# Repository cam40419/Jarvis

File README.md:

# Simon

**SIMON: Somehow It Manages Our Nonsense.**

Simon is a local-first foundation for a hosted AI work platform. Its browser workspace
currently provides shared projects, task boards, human membership and scoped agent teams,
alongside independent conversations. PostgreSQL persists project and identity records.

In **Projects**, describe an outcome, create tasks, and assign work to a person, an agent
or the shared pool. **Agents** defines each role's responsibilities, success criteria and
reason for joining the team. Owners control team size, delegated staffing and temporary
worker access. Pausing or retiring an agent returns unfinished assignments to the pool.

**Intake** accepts versioned source files, uses a configured model to propose the next
milestone and team, and makes a separate model review before applying roles and board work.
**Models & usage** provides write-only project keys, deliberate model qualification,
separate planning/review routes, and shared project/workspace spending and call limits.
Projects control hosted/paid consent and automatic staffing. Unknown usage remains held
until settled or reconciled with evidence. **Execution** queues bounded agent workflows,
tracks checkpoints, dependencies, questions, delegation and schedules, and saves text
candidates for review. An optional outbound runner advances server-side steps under a
separate owner grant. **Artifacts & review** saves immutable output versions, performs
independent text review, records exact-version acceptance and creates linked repair work
from owner feedback. **Delivery packets** bundles exact originals, safe source previews,
checks, decisions and limitations, with immutable history and current-access checks.
Compute/storage entitlements and broader quality evaluation remain
subsequent core work. Creating a role does not start a worker.
The old Work interface, manifest dispatcher and separate project/task authorities have
been removed. There is no legacy-project migration or compatibility mode.

## Run locally

Use Python 3.11+ and a local virtual environment:

```powershell
python -m venv venv
.\venv\Scripts\python.exe -m pip install -e '.[dev,postgres]'
```

Configure `.env` from [.env.example](.env.example). For a configured local installation,
start the Compose database with `.\scripts\start-local.ps1 -DatabaseOnly` when using that local database, then start the configured server with `.\scripts\start-local.ps1` and open
**http://localhost:8000/login**. Independent queued conversations use
`.\scripts\start-assistant-worker.ps1`; this does not execute native board tasks.
New installations can use `.\scripts\start-dev.ps1 -Memory -TestRunner` for a
nonpersistent smoke run. Follow [identity setup](docs/runbooks/identity.md) and
[local operations](docs/runbooks/local-operations.md) for persistent accounts.

## Guides

- [Projects, scoped agents and team management](docs/runbooks/native-projects.md)
- [AI-assisted intake and automatic staffing](docs/runbooks/project-intake.md)
- [Project models, encrypted keys and resource limits](docs/runbooks/project-models.md)
- [Native execution, durable workflows and runners](docs/runbooks/native-execution.md)
- [Artifacts, independent review and owner revisions](docs/runbooks/native-artifacts.md)
- [Roadmap and delivery order](docs/next-phases.md)
- [Platform architecture and implementation backlog](docs/architecture/autonomous-work-platform-plan.md)
- [Clothing-brand pilot and core acceptance](docs/architecture/clothing-brand-pilot-charter.md)
- [Integration work packages](docs/architecture/integration-delivery-plan.md)
- [Hosting and subscription capacity](docs/architecture/hosting-and-capacity-plan.md)
- [Development standards](docs/development.md)
- [Isolated database testing](docs/runbooks/database-testing.md)
- [Storage recovery](docs/runbooks/storage-recovery.md) and [remote access](docs/runbooks/remote-access.md)

The platform is the deliverable; stdout is its pilot. Complete and test the core before
accepting individual business tools. Existing generic adapters are reusable implementation
components, not accepted native-project integrations.

## Verify

```powershell
.\venv\Scripts\python.exe -m ruff check src tests scripts examples
.\venv\Scripts\python.exe -m ruff format --check src tests scripts examples
.\venv\Scripts\python.exe -m mypy src
.\venv\Scripts\python.exe -m pytest -q -m "not postgres and not browser and not live"
npm run format:check
npm run lint
```

PostgreSQL tests use an isolated database ending in `_test`; the database runbook describes
the disposable-cluster runner. Browser tests use `SIMON_BROWSER_TESTS=1` and installed
Playwright Chromium or `SIMON_BROWSER_CHANNEL=msedge`. Normal acceptance uses synthetic
providers. Paid model tests require separate explicit opt-in.

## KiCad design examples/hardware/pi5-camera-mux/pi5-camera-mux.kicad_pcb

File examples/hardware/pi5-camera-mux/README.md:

# Raspberry Pi 5 four-camera selector: engineering prototype

This review project connects **four IMX219 Camera Module 2 cameras, with one CSI
camera selected at a time**, to a Raspberry Pi 5 camera connector. It implements
three two-to-one TS3DV642-Q1 switches, a PCA9544A I2C selector at address `0x70`,
and a separately supplied camera rail. It is a CAD prototype awaiting physical
electrical, signal-integrity, cable and Raspberry Pi software validation.

**Use an external regulated, current-limited 3.3 V supply at J7.** Never connect
5 V to that header. The Pi connector powers the switch/control rail; it does not
supply the four camera modules. A TPS22918 gates the external camera rail from
the Pi's 3.3 V presence. It is not a regulator, current limiter or reverse-current
protector. A 1.5 A current limit is an initial bench setup, not a measured demand
or guaranteed operating budget. All four modules may be powered for enumeration.

## Review files

- Open `pi5-camera-mux.kicad_pro` in KiCad 9; the corresponding schematic and PCB
  are editable source. `CameraMux.kicad_sym` and library tables accompany them.
- `review/schematic.pdf` and `review/board.png` provide browser previews.
- `review/schematic-details.pdf` retains the master and adds nine enlarged A4
  section pages for reading and printing; its companion JSON records provenance.
- `review/bom.csv`, `review/connectivity.net`, and `review/gerbers-review.zip`
  provide the BOM, actual exported netlist, and Gerber/Excellon review package.
- `review/erc.json`, `review/drc.json`, and `review/tool-smoke.json` contain the
  actual KiCad tool results. A nonzero violation count remains a release hold.
- `connectivity-review.json` and `review/layout-review.json` record independent
  pin, board/netlist, trace-length, layer, via and plane observations.
- [engineering-review.md](engineering-review.md) records manufacturer references,
  component pin tables, power/driver analysis and the outstanding release checks.

The Gerber ZIP is for engineering review. Do not order or assemble this revision
until the documented release holds have been resolved by an electronics reviewer.

Validation recorded on 2026-10-01 UTC with KiCad 9.0.2:

- All seven isolated PCB operations completed successfully. ERC: **0 violations**.
  DRC: **0 violations, 0 missing connections, 0 schematic-parity issues**.
- The workspace Python tool successfully invoked Debian's `pcbnew` interpreter
  to load and save an editable board; source hashes remained unchanged and the
  container lease was released. An attempted output overwrite was rejected.
- Independent review passed **225 netlist checks**, found no board-pad/netlist
  mismatches, and confirmed all 42 CSI nets are simple, unbranched front-layer
  paths. All 21 measured pairs have **0.0000 mm P/N difference** and zero vias.
- All **24,438 ground-reference samples** beneath CSI traces fall within one
  filled In1 ground region. This is sampled geometry, not electromagnetic analysis.
- Selected board copper paths measure **109.5515–113.6643 mm**, excluding switch
  packages and cables. Lane-to-clock length differences and total insertion loss
  remain subjects for signal-integrity qualification and physical tests.

The reviewed board SHA-256 is
`dcc29d94eef476e0034d6c41a2a14266b6fae18dcd7bfd40f2587fa7990fcb64`.
No physical board, camera capture, impedance measurement or fabrication was performed.

## Connections and assembly

| Connector | Purpose | Key details |
| --- | --- | --- |
| J1 | Pi 5 host | Amphenol F32Q-1A7H1-11022, 22 positions, 0.5 mm, top contacts |
| J2/J3/J4/J5 | Cameras A/B/C/D | TE 1-84953-5, 15 positions, 1 mm, top contacts |
| J6 | Pi GPIO control | Pins 1–4: GND, GPIO4, GPIO17, GPIO18 |
| J7 | External camera power | Pin 1 regulated 3.3 V; pin 2 common ground |

Camera connector pin 11 shares the host camera-enable IO0. Pin 12 IO1 connects
through separate **DNP** zero-ohm links R16–R19; leave all four links unfitted for
Camera Module 2, whose official schematic marks pin 12 unconnected. R6/R7 host
I2C pull-ups are also DNP. Check the combined module/board pull-up resistance
before fitting the downstream pull-ups R8–R15.

Read board pin-1 markings and manufacturer contact drawings, and verify every
cable's conductor continuity before applying power. A pitch adapter cable alone
does not establish contact orientation. The TE signal/mounting-pad drawing review
is recorded in the engineering review; actual mating cable clearances, connector
samples and host cable orientation still require assembly validation.
On the board top view, pin 1 is below the last/supply pin on all five FFC
connectors. J1's host cable may extend over the board: confirm insertion direction,
actuator access and physical cable clearance with the actual connector samples.

The GPIO4/18/17 selection states are A=`0/1/0`, B=`1/1/0`, C=`0/0/1`,
D=`1/0/1`. GPIO pull-downs disable both leaf switches at reset. Do not switch
cameras during capture. Use a reviewed device-tree/libcamera configuration to
coordinate video selection and I2C selection; the candidate official overlay in
the engineering review has not been tested on this physical board.

## Layout intent and limits

The board is 125 × 110 mm with four copper layers: F.Cu carries the paired CSI
paths, In1.Cu supplies their ground reference, In2.Cu distributes camera power,
and B.Cu carries control/auxiliary routes. The CSI paths use 0.15 mm copper and
0.22 mm pair gap in their trunks, with short symmetric pad fanouts and no signal
vias. These dimensions are geometric choices, **not a verified 100-ohm stack-up**.

The independent layout report measures each of 21 differential pairs and the
three board segments in each selectable path. Package internals and FFC cables
are excluded. Two switch stages, path length, connector discontinuities and
the actual fabricated stack-up require signal-integrity review and bench tests.
Ground plane fill is checked geometrically; this does not replace return-current
and via-antipad review. Plane necks, supply drop, inrush, thermal behavior and
backfeeding under every power sequence require measurement.

## Reproducing the CAD workflow

Use a **copy** of this directory. Generation replaces the source board with the
deterministic placement and locked paired routes; the final low-speed routing
comes from the separately imported router session. Ground/power vias are fixed
before routing; KiCad supplies the final internal-plane fill after import. The
router receives those fixed conductors without plane polygons, avoiding its
incomplete SMD-to-plane handling on disabled inner routing layers.

```powershell
docker build -f deploy/Dockerfile.pcb-worker -t simon-pcb:local .
docker build -f deploy/Dockerfile.pcb-router -t simon-pcb-router:local .
$pcbProject = (Resolve-Path 'path/to/project-copy').Path
docker run --rm --network none --mount "type=bind,source=$pcbProject,target=/workspace" --entrypoint /usr/bin/python3 simon-pcb:local /workspace/generate.py
docker run --rm --hostname localhost --network none --cpus 2 --memory 2g --mount "type=bind,source=$pcbProject,target=/workspace" --entrypoint /opt/java/openjdk/bin/java simon-pcb-router:local -jar /opt/freerouting.jar -de /workspace/pi5-camera-mux.dsn -do /workspace/pi5-camera-mux.ses --gui.enabled=false -mp 20 -mt 0 --router.layers.routable=true,false,false,true -da --api_server.enabled=false --user_data_path=/tmp/freerouting
docker run --rm --network none --mount "type=bind,source=$pcbProject,target=/workspace" --entrypoint /usr/bin/python3 simon-pcb:local /workspace/finish_routing.py
```

The optional router image pins Freerouting 2.4.1 by SHA-256 and uses Java 25.
Routing runs offline, preserves fixed CSI geometry, and may require manual
completion/review after tool or library changes. Inspect actual DRC rather than
assuming an autorouter's completion message establishes a correct board.

From the repository root, refresh real isolated-tool exports with
`python examples/agents/pcb_smoke.py --write-review`. Refresh the independent
connectivity audit with `python examples/hardware/pi5-camera-mux/review_connectivity.py`.
Run `review_layout.py` using KiCad's `/usr/bin/python3` and save its JSON output.
`render_preview.py` rasterizes the actual SVG using PyMuPDF; `schematic_details.py`
uses the same development dependency to create vector-preserving enlarged pages.
These scripts use no model/provider calls. See the
[PCB tool runbook](../../../docs/runbooks/agent-pcb.md) for authorization and limits.

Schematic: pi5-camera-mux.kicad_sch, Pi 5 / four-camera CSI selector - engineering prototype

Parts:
C1, C2, C3, C4: 100nF; C_0603_1608Metric
C5, C6: 10uF_10V_X5R; C_0805_2012Metric
C7: 1nF; C_0603_1608Metric
J1: F32Q-1A7H1-11022_HOST; Amphenol_F32Q-1A7x1-11022_1x22-1MP_P0.5mm_Horizontal
J2: TE_1-84953-5_CAM_A; TE_1-84953-5_1x15-1MP_P1.0mm_Horizontal
J3: TE_1-84953-5_CAM_B; TE_1-84953-5_1x15-1MP_P1.0mm_Horizontal
J4: TE_1-84953-5_CAM_C; TE_1-84953-5_1x15-1MP_P1.0mm_Horizontal
J5: TE_1-84953-5_CAM_D; TE_1-84953-5_1x15-1MP_P1.0mm_Horizontal
J6: GPIO_GND_4_17_18; PinHeader_1x04_P2.54mm_Vertical
J7: REGULATED_3V3_INPUT; PinHeader_1x02_P2.54mm_Vertical
R1, R2, R3: 10k; R_0603_1608Metric
R4: 100k; R_0603_1608Metric
R5: 100R; R_0603_1608Metric
R6, R7: 4.7k_DNP; R_0603_1608Metric; not fitted
R8, R9, R10, R11, R12, R13, R14, R15: 4.7k; R_0603_1608Metric
R16, R17, R18, R19: 0R_DNP_IO1; R_0603_1608Metric; not fitted
U1, U2, U3: TS3DV642RUARQ1; WQFN-42-1EP_3.5x9mm_P0.5mm_EP2.05x7.55mm
U4: PCA9544APWR_ADDR_0x70; Texas_PW0020A_TSSOP-20_4.4x6.5mm_P0.65mm
U5: TPS22918DBVR; SOT-23-6

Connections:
/BANK_AB_CLK_N: U1.37 (D0-A), U2.6 (D0-)
/BANK_AB_CLK_P: U1.38 (D0+A), U2.5 (D0+)
/BANK_AB_D0_N: U1.33 (D2-A), U2.11 (D2-)
/BANK_AB_D0_P: U1.34 (D2+A), U2.10 (D2+)
/BANK_AB_D1_N: U1.35 (D1-A), U2.8 (D1-)
/BANK_AB_D1_P: U1.36 (D1+A), U2.7 (D1+)
/BANK_CD_CLK_N: U1.28 (D0-B), U3.6 (D0-)
/BANK_CD_CLK_P: U1.29 (D0+B), U3.5 (D0+)
/BANK_CD_D0_N: U1.24 (D2-B), U3.11 (D2-)
/BANK_CD_D0_P: U1.25 (D2+B), U3.10 (D2+)
/BANK_CD_D1_N: U1.26 (D1-B), U3.8 (D1-)
/BANK_CD_D1_P: U1.27 (D1+B), U3.7 (D1+)
/CAM_3V3: C6.1, J2.15 (CAM_3V3), J3.15 (CAM_3V3), J4.15 (CAM_3V3), J5.15 (CAM_3V3), R5.2, R8.2, R9.2, R10.2, R11.2, R12.2, R13.2, R14.2, R15.2, U5.6 (VOUT)
/CAM_A_CLK_N: J2.8 (CAM_A_CLK_N), U2.37 (D0-A)
/CAM_A_CLK_P: J2.9 (CAM_A_CLK_P), U2.38 (D0+A)
/CAM_A_D0_N: J2.2 (CAM_A_D0_N), U2.33 (D2-A)
/CAM_A_D0_P: J2.3 (CAM_A_D0_P), U2.34 (D2+A)
/CAM_A_D1_N: J2.5 (CAM_A_D1_N), U2.35 (D1-A)
/CAM_A_D1_P: J2.6 (CAM_A_D1_P), U2.36 (D1+A)
/CAM_A_IO1: J2.12 (CAM_A_IO1), R16.2
/CAM_A_SCL: J2.13 (CAM_A_SCL), R8.1, U4.6 (SC0)
/CAM_A_SDA: J2.14 (CAM_A_SDA), R9.1, U4.5 (SD0)
/CAM_B_CLK_N: J3.8 (CAM_B_CLK_N), U2.28 (D0-B)
/CAM_B_CLK_P: J3.9 (CAM_B_CLK_P), U2.29 (D0+B)
/CAM_B_D0_N: J3.2 (CAM_B_D0_N), U2.24 (D2-B)
/CAM_B_D0_P: J3.3 (CAM_B_D0_P), U2.25 (D2+B)
/CAM_B_D1_N: J3.5 (CAM_B_D1_N), U2.26 (D1-B)
/CAM_B_D1_P: J3.6 (CAM_B_D1_P), U2.27 (D1+B)
/CAM_B_IO1: J3.12 (CAM_B_IO1), R17.2
/CAM_B_SCL: J3.13 (CAM_B_SCL), R10.1, U4.9 (SC1)
/CAM_B_SDA: J3.14 (CAM_B_SDA), R11.1, U4.8 (SD1)
/CAM_C_CLK_N: J4.8 (CAM_C_CLK_N), U3.37 (D0-A)
/CAM_C_CLK_P: J4.9 (CAM_C_CLK_P), U3.38 (D0+A)
/CAM_C_D0_N: J4.2 (CAM_C_D0_N), U3.33 (D2-A)
/CAM_C_D0_P: J4.3 (CAM_C_D0_P), U3.34 (D2+A)
/CAM_C_D1_N: J4.5 (CAM_C_D1_N), U3.35 (D1-A)
/CAM_C_D1_P: J4.6 (CAM_C_D1_P), U3.36 (D1+A)
/CAM_C_IO1: J4.12 (CAM_C_IO1), R18.2
/CAM_C_SCL: J4.13 (CAM_C_SCL), R12.1, U4.13 (SC2)
/CAM_C_SDA: J4.14 (CAM_C_SDA), R13.1, U4.12 (SD2)
/CAM_D_CLK_N: J5.8 (CAM_D_CLK_N), U3.28 (D0-B)
/CAM_D_CLK_P: J5.9 (CAM_D_CLK_P), U3.29 (D0+B)
/CAM_D_D0_N: J5.2 (CAM_D_D0_N), U3.24 (D2-B)
/CAM_D_D0_P: J5.3 (CAM_D_D0_P), U3.25 (D2+B)
/CAM_D_D1_N: J5.5 (CAM_D_D1_N), U3.26 (D1-B)
/CAM_D_D1_P: J5.6 (CAM_D_D1_P), U3.27 (D1+B)
/CAM_D_IO1: J5.12 (CAM_D_IO1), R19.2
/CAM_D_SCL: J5.13 (CAM_D_SCL), R14.1, U4.16 (SC3)
/CAM_D_SDA: J5.14 (CAM_D_SDA), R15.1, U4.15 (SD3)
/CAM_IO0: J1.17 (CAM_IO0), J2.11 (CAM_IO0), J3.11 (CAM_IO0), J4.11 (CAM_IO0), J5.11 (CAM_IO0)
/DISCHARGE: R5.1, U5.5 (QOD)
/EXT_3V3: C5.1, J7.1 (EXT_3V3), U5.1 (VIN)
/GND: C1.2, C2.2, C3.2, C4.2, C5.2, C6.2, C7.2, J1.1 (GND), J1.4 (GND), J1.7 (GND), J1.10 (GND), J1.13 (GND), J1.16 (GND), J1.19 (GND), J2.1 (GND), J2.4 (GND), J2.7 (GND), J2.10 (GND), J3.1 (GND), J3.4 (GND), J3.7 (GND), J3.10 (GND), J4.1 (GND), J4.4 (GND), J4.7 (GND), J4.10 (GND), J5.1 (GND), J5.4 (GND), J5.7 (GND), J5.10 (GND), J6.1 (GND), J7.2 (GND), R1.2, R2.2, R3.2, R4.2, U1.43 (EP_GND), U2.43 (EP_GND), U3.43 (EP_GND), U4.1 (A0), U4.2 (A1), U4.3 (A2), U4.10 (GND), U5.2 (GND)
/GPIO4_PORT: J6.2 (GPIO4_PORT), R1.1, U2.17 (SEL2), U3.17 (SEL2)
/GPIO17_BANK: J6.3 (GPIO17_BANK), R2.1, U1.17 (SEL2), U3.2 (EN)
/GPIO18_EN_AB: J6.4 (GPIO18_EN_AB), R3.1, U2.2 (EN)
/HOST_3V3: C1.1, C2.1, C3.1, C4.1, J1.22 (HOST_3V3), R4.1, R6.2, R7.2, U1.1 (VCC), U1.2 (EN), U1.16 (SEL1), U2.1 (VCC), U2.16 (SEL1), U3.1 (VCC), U3.16 (SEL1), U4.4 (INT0), U4.7 (INT1), U4.11 (INT2), U4.14 (INT3), U4.20 (VCC), U5.3 (ON)
/HOST_CLK_N: J1.8 (HOST_CLK_N), U1.6 (D0-)
/HOST_CLK_P: J1.9 (HOST_CLK_P), U1.5 (D0+)
/HOST_D0_N: J1.2 (HOST_D0_N), U1.11 (D2-)
/HOST_D0_P: J1.3 (HOST_D0_P), U1.10 (D2+)
/HOST_D1_N: J1.5 (HOST_D1_N), U1.8 (D1-)
/HOST_D1_P: J1.6 (HOST_D1_P), U1.7 (D1+)
/HOST_IO1: J1.18 (HOST_IO1), R16.1, R17.1, R18.1, R19.1
/HOST_SCL: J1.20 (HOST_SCL), R6.1, U4.18 (SCL)
/HOST_SDA: J1.21 (HOST_SDA), R7.1, U4.19 (SDA)
/SLEW_CT: C7.1, U5.4 (CT)

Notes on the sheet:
SIGNAL TREE | Switch channels D0=CSI clock, D1=CSI DATA1, D2=CSI DATA0
CONTROL / PCA9544A address 0x70; individual downstream I2C buses
POWER / regulated external 3.3V, current-limited supply; common ground
DECOUPLING AND CONTROL | 10k GPIO pulls disable both leaf switches at reset
A: GPIO4/18/17 = 0/1/0; B = 1/1/0; C = 0/0/1; D = 1/0/1
Camera IO0 is common for probing. IO1 links R16-R19 are DNP pending camera-specific review.
R6/R7 DNP: host pull-ups normally present. Check parallel module pull-ups before fitting R8-R15.

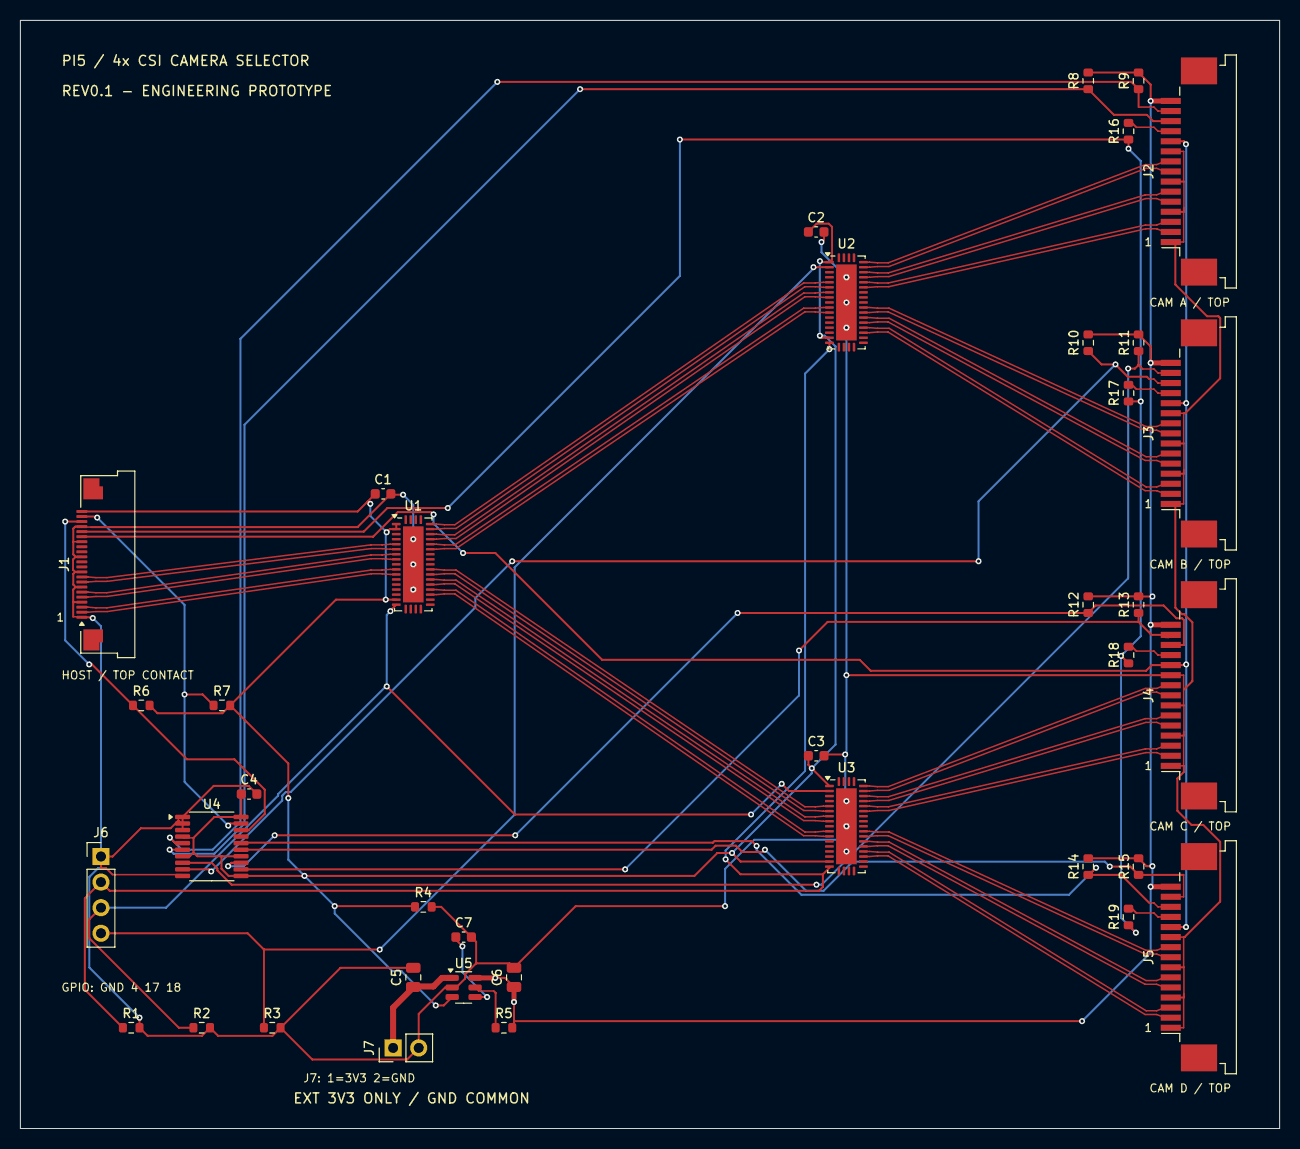
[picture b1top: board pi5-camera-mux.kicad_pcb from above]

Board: 4 copper layers, 125.0 x 110.0 mm, 38 parts (0 on the bottom side), 67 nets.

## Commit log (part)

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2025-09-18 Schemas for the memory storage
2025-09-22 A new look on the context building process
2025-09-25 Stuff
2025-09-25 resimplify agent
2025-09-26 Better router scheme, deep run and tools still needed
2025-10-22 Tool usage and basic memory
2025-10-22 Half working calendar
